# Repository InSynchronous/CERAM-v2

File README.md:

# CERAM

Cost Effective Rocket Aviation Module.

CERAM is a flight computer board for model rocketry, built around a simple idea: instead of hand soldering a big board full of tiny SMD parts, you plug in cheap breakout boards that cost a couple of dollars each. The board just wires them together.

## Why

Making a rocket flight computer usually means picking one of two paths. Either you buy a commercial unit and spend a lot of money, or you design your own PCB with a bare microcontroller, an IMU, a barometer and a pile of passives, then try to hand solder QFN packages with a normal iron. The second option likely results in failure.

## What is on it

CERAM is a carrier board. What goes on top of it defines its actual use.

- A Seeed Studio Xiao ESP32-S3 board serving as the MCU of the entire stack
- An MPU-6050 or other compatible IMU
- A BMP280 or other compatible barometer
- 4 PWM outputs
- A UART Header
- An I2C Header
- A LM317 for voltage regulation
- Two IRLZ44N MOSFETs for parachute deployment/reaction wheel driving/motor igniting/pyrotechnic uses

## BOM

| Part | Link | Cost |
|---|---|---|
| Screw Terminals 5.08mm | <https://www.aliexpress.us/item/2251832621219818.html> | $1.96 |
| Resistor Kit (not requesting) (1x 220ohm 2x 330ohm 3x 10k ohm) | <https://www.aliexpress.us/item/3256808562766775.html> | $3.17 |
| IRLZ44N (not requesting)| <https://www.aliexpress.us/item/3256807934257560.html> | $2.30 |
| LM317 | <https://www.aliexpress.us/item/3256803468041967.html> | $1.91 |
| Header Pins | <https://www.aliexpress.us/item/3256807247428541.html> | $1.84 |
| Seeed Studio Xiao ESP32-S3 (equal to or less than aliexpress pricing when including shipping charges) | <https://www.amazon.com/ESP32S3-2-4GHz-Dual-core-Supported-Efficiency-Interface/dp/B0BYSB66S5> | $16.99 |
| BMP280 (aliexpress only has fake clones trust me) | <https://www.amazon.com/Atmospheric-Pressure-Modules-Barometric-Compatible/dp/B0FDWN2LVS/> | $6.62 |
| MPU6050 | <https://www.aliexpress.us/item/3256809482368154.html> | $2.82 |
| JLC PCB | (see CERAM-V2.zip in pcb/production) | $5.30 |
| Total | . | $42.91 |

## Software
Included is a board test program (`firmware/BoardTest`) that initializes the IMU, barometer, and servos and streams all sensor readings over serial.
Please use the build.sh command to build and flash (you may need to change ports).

## Software
Included is a board test program (`firmware/BoardTest`) that initializes the IMU, barometer, and servos and streams all sensor readings over serial.

### Uploading

1. Install [arduino-cli](https://arduino.github.io/arduino-cli/latest/installation/) and the ESP32 board core
2. Set `PORT` and `FQBN` at the top of `firmware/build.sh` to match your XIAO
3. Run `./build.sh` - it compiles, flashes, and opens the serial monitor. `./serial.sh` opens just the monitor

### What it outputs

- On boot the IMU self-calibrates and prints its drift
- Every 10ms it streams one line over serial: timestamp, accel (m/s2), gyro (deg/s), IMU temp, baro temp/pressure/altitude, attitude (roll/pitch/yaw), and servo commands
- Servo commands are PID leveled, clamped to +/-30 of center, on GPIO 9 (inner) and GPIO 2 (outer)
- The LED on GPIO 4 blinks every 500ms. If it stops, the loop is hung.

## PCB
Completed gerbers can be found in `pcb/production/CERAM-V2.zip` and `gerbers.zip`.

### Ordering the PCB
Upload `pcb/production/CERAM-V2.zip` to your PCBA source of choice. I like JLCPCB and live in the West Coast of America.
All the gerber layers and drill files are inside. Pick **2 layers, 1.6mm board**, 
Check the outline, silkscreen, and drill with `images/3.png` for safety just in case something screws up. 

### Schematic

### PCB

## Known Issues
The Xiao seeed studio chip may have some difficulties mounting according to online reports. I've never had an issue with it myself, but note you may need to bend some pins.

## Credits
I used the Seeed Studio Fusion Open Parts Library (OPL)

## License
MIT. See LICENSE.

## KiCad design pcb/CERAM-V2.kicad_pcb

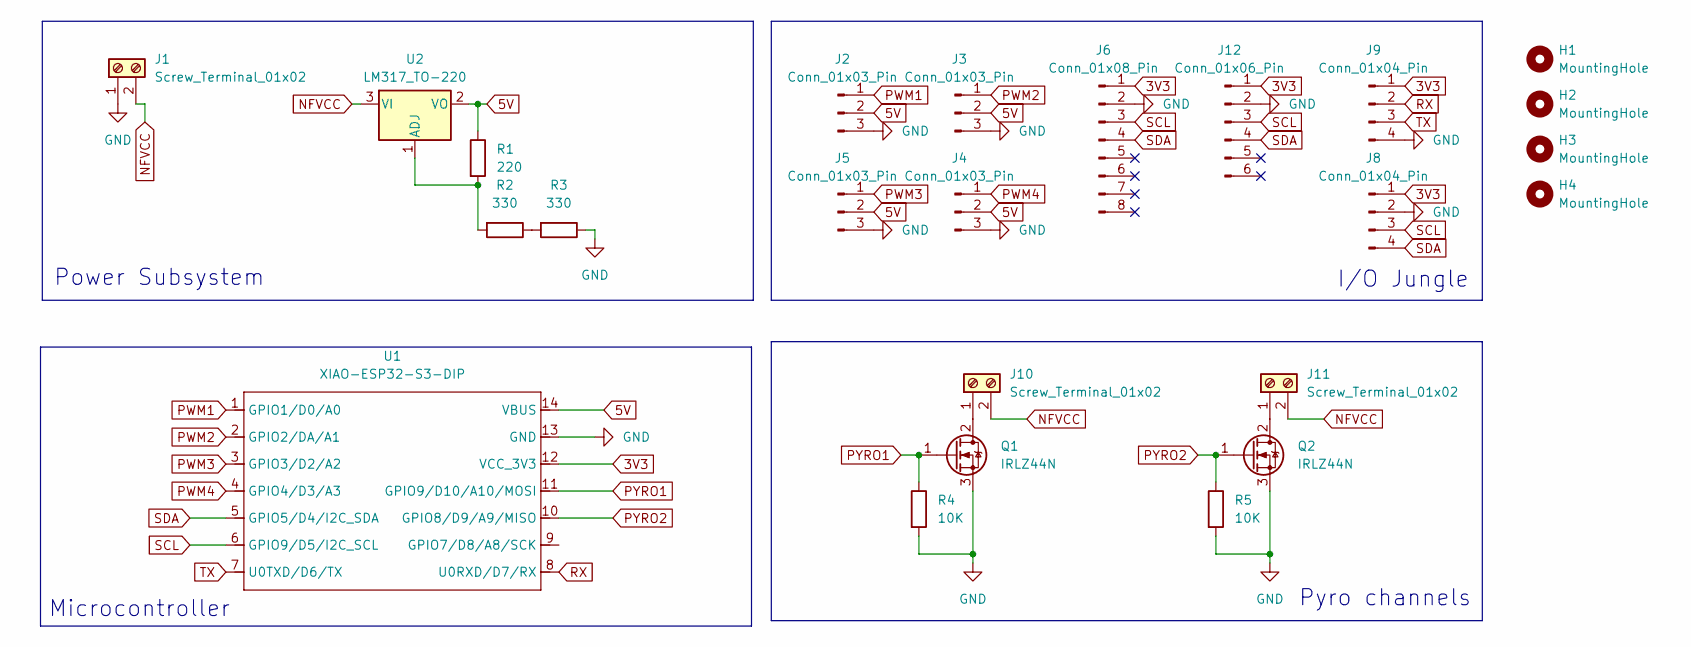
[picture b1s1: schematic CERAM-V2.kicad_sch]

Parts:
H1, H2, H3, H4: MountingHole; MountingHole_3.2mm_M3
J1, J10, J11: Screw_Terminal_01x02; TerminalBlock_Phoenix_MKDS-1,5-2-5.08_1x02_P5.08mm_Horizont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
J2, J3, J4, J5: Conn_01x03_Pin; PinHeader_1x03_P2.54mm_Vertical
J6: Conn_01x08_Pin; PinHeader_1x08_P2.54mm_Vertical
J8, J9: Conn_01x04_Pin; PinHeader_1x04_P2.54mm_Vertical
J12: Conn_01x06_Pin; PinHeader_1x06_P2.54mm_Vertical
Q1, Q2: IRLZ44N; TO-220-3_Vertical
R1: 220; R_Axial_DIN0207_L6.3mm_D2.5mm_P7.62mm_Horizontal
R2, R3: 330; R_Axial_DIN0207_L6.3mm_D2.5mm_P7.62mm_Horizontal
R4, R5: 10K; R_Axial_DIN0207_L6.3mm_D2.5mm_P7.62mm_Horizontal
U1: XIAO-ESP32-S3-DIP; XIAO-ESP32S3-DIP
U2: LM317_TO-220; TO-220-3_Vertical

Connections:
3V3: J6.1, J8.1, J9.1, J12.1, U1.12 (VCC_3V3)
5V: J2.2, J3.2, J4.2, J5.2, R1.1, U1.14 (VBUS), U2.2 (VO)
GND: J1.1, J2.3, J3.3, J4.3, J5.3, J6.2, J8.2, J9.4, J12.2, Q1.3 (S), Q2.3 (S), R3.1, R4.2, R5.2, U1.13 (GND)
NFVCC: J1.2, J10.2, J11.2, U2.3 (VI)
unnamed: J10.1, Q1.2 (D)
unnamed: J11.1, Q2.2 (D)
unnamed: R2.1, R3.2
unnamed: R1.2, R2.2, U2.1 (ADJ)
PWM1: J2.1, U1.1 (GPIO1/D0/A0)
PWM2: J3.1, U1.2 (GPIO2/DA/A1)
PWM3: J5.1, U1.3 (GPIO3/D2/A2)
PWM4: J4.1, U1.4 (GPIO4/D3/A3)
PYRO1: Q1.1 (G), R4.1, U1.11 (GPIO9/D10/A10/MOSI)
PYRO2: Q2.1 (G), R5.1, U1.10 (GPIO8/D9/A9/MISO)
RX: J9.2, U1.8 (U0RXD/D7/RX)
SCL: J6.3, J8.3, J12.3, U1.6 (GPIO9/D5/I2C_SCL)
SDA: J6.4, J8.4, J12.4, U1.5 (GPIO5/D4/I2C_SDA)
TX: J9.3, U1.7 (U0TXD/D6/TX)

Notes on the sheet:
I/O Jungle
Microcontroller
Pyro channels
Power Subsystem

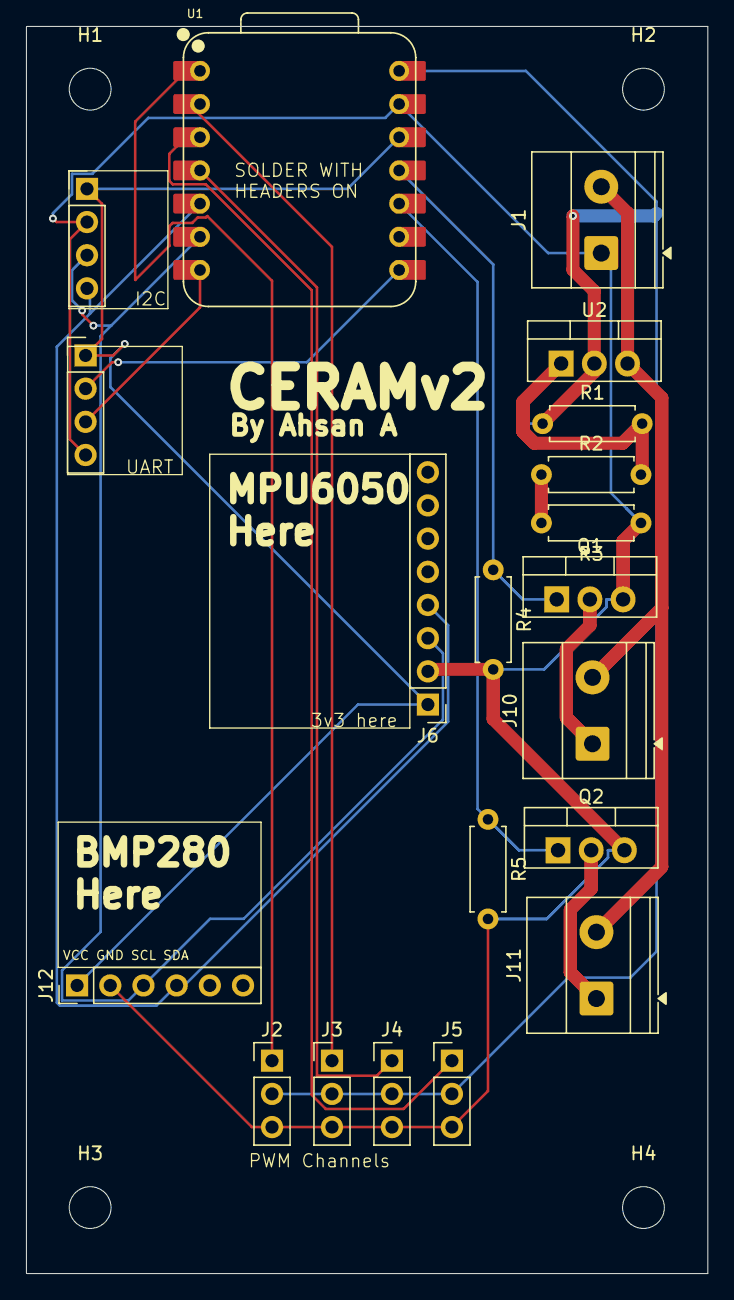
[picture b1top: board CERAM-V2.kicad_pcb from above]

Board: 2 copper layers, 52.2 x 95.5 mm, 24 parts (0 on the bottom side), 18 nets.

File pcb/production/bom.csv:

Designator,Footprint,Quantity,Value,LCSC Part #
"J1, J10, J11","TerminalBlock_Phoenix_MKDS-1,5-2-5.08_1x02_P5.08mm_Horizontal",3,Screw_Terminal_01x02,
J12,PinHeader_1x06_P2.54mm_Vertical,1,Conn_01x06_Pin,
"J2, J3, J4, J5",PinHeader_1x03_P2.54mm_Vertical,4,Conn_01x03_Pin,
J6,PinHeader_1x08_P2.54mm_Vertical,1,Conn_01x08_Pin,
"J8, J9",PinHeader_1x04_P2.54mm_Vertical,2,Conn_01x04_Pin,
"Q1, Q2",TO-220-3_Vertical,2,IRLZ44N,
R1,R_Axial_DIN0207_L6.3mm_D2.5mm_P7.62mm_Horizontal,1,220,
"R2, R3",R_Axial_DIN0207_L6.3mm_D2.5mm_P7.62mm_Horizontal,2,330,
"R4, R5",R_Axial_DIN0207_L6.3mm_D2.5mm_P7.62mm_Horizontal,2,10K,
U1,XIAO-ESP32S3-DIP,1,XIAO-ESP32-S3-DIP,
U2,TO-220-3_Vertical,1,LM317_TO-220,
